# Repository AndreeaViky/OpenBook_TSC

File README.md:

# OpenBook

## Block Diagram

## Implementation steps

1. Schematic Design

   - The schematic was created based on the provided electrical diagram.
   - Components were added using the DeskAssistant library.
   - An Electrical Rules Check (ERC) was performed to ensure there were no errors or missing connections.

2. PCB Layout

   - The schematic was transferred to the PCB editor using "Switch to PCB."
   - Components were arranged according to the layout reference.
   - The board outline was drawn to the required dimensions, including necessary cutouts.
   - Key components were positioned first for visibility, while resistors and capacitors were placed based on their proximity in the schematic.
   - Auto-routing was performed on both the top and bottom layers using a 0.15 mm trace width.
   - Power traces were manually adjusted to have a minimum width of 0.30 mm for proper current handling.
   - Ground planes were created using the GND signal, followed by via stitching to improve ground continuity.
   - Most stitching vias were placed around the antenna area for enhanced grounding and RF performance.

3. 3D Components

   - 3D models were assigned in the schematic using the [Component Search Engine] (https://componentsearchengine.com).
   - Models were accurately aligned based on their footprints for realistic placement in 3D view.

4. Case Update

   - After placing the PCB inside the enclosure, the case design was modified to accommodate connectors.
   - Adjustments were made to ensure all ports were accessible and properly aligned.

5. Custom 3D Models
   - 3D models for the enclosure and display were created based on technical drawings and datasheets.
   - These models were then placed into the final assembly to verify fit and alignment.

## Bill of Materials (BOM)

| Component                | Link                                                                                                                       | Datasheet                                                                                                                                                                                                                                    |
| ------------------------ | -------------------------------------------------------------------------------------------------------------------------- | -------------------------------------------------------------------------------------------------------------------------------------------------------------------------------------------------------------------------------------------- |
| BME680                   | [Model](https://www.snapeda.com/parts/BME680/Bosch/view-part/?welcome=home)                                                | [Datasheet](//efaidnbmnnnibpcajpcglclefindmkaj/https://www.bosch-sensortec.com/media/boschsensortec/downloads/datasheets/bst-bme680-ds001.pdf)                                                                                               |
| BUTTON                   | [Model](https://industry.panasonic.com/global/en/products/control/switch/light-touch/number/evqpuj02k)                     | [Datasheet](https://www.lcsc.com/datasheet/lcsc_datasheet_2201121800_PANASONIC-EVQPUJ02K_C2936858.pdf)                                                                                                                                       |
| CAPACITOR                | [Model](<https://componentsearchengine.com/part-view/R0402%201%25%20100%20K%20(RC0402FR-07100KL)/YAGEO>)                   | [Datasheet](//efaidnbmnnnibpcajpcglclefindmkaj/https://www.resistor.com/assets/pdf/0402tstd.pdf)                                                                                                                                             |
| R0402                    | [Model](<https://componentsearchengine.com/part-view/R0402%201%25%20100%20K%20(RC0402FR-07100KL)/YAGEO>)                   | [Datasheet](//efaidnbmnnnibpcajpcglclefindmkaj/https://www.resistor.com/assets/pdf/0402tstd.pdf)                                                                                                                                             |
| CPH3225A                 | [Model](https://www.snapeda.com/parts/CPH3225A/Seiko+Instruments/view-part/?ref=eda)                                       | [Datasheet](https://octopart.com/datasheet/cph3225a-seiko-25340571)                                                                                                                                                                          |
| EVQPUJ02K                | [Model](https://industry.panasonic.com/global/en/products/control/switch/light-touch/number/evqpuj02k)                     | [Datasheet](https://www.lcsc.com/datasheet/lcsc_datasheet_2201121800_PANASONIC-EVQPUJ02K_C2936858.pdf)                                                                                                                                       |
| KP-1608SURCK             | [Model](https://www.snapeda.com/parts/KP-1608SURCK/Kingbright/view-part/?ref=search&t=LED%200603)                          | [Datasheet](//efaidnbmnnnibpcajpcglclefindmkaj/https://media.elv.com/file/107153_led_surck1608_data.pdf)                                                                                                                                     |
| USBLC6-2SC6Y             | [Model](https://www.snapeda.com/parts/USBLC6-2SC6Y/STMicroelectronics/view-part/?ref=eda)                                  | [Datasheet](https://www.digikey.com/en/htmldatasheets/production/1375342/0/0/1/usblc6-2sc6y)                                                                                                                                                 |
| SD0805S020S1R0           | [Model](https://ro.mouser.com/ProductDetail/KYOCERA-AVX/SD0805S020S1R0?qs=jCA%252BPfw4LHbpkAoSnwrdjw%3D%3D)                | [Datasheet](https://www.alldatasheet.com/view.jsp?Searchword=SD0805S&sField=2)                                                                                                                                                               |
| PGB1010603MR             | [Model](https://www.snapeda.com/parts/PGB1010603MR/Littelfuse/view-part/?ref=eda)                                          | [Datasheet](https://www.alldatasheet.com/view.jsp?Searchword=Pgb1010603mr&gad_source=1&gbraid=0AAAAADcdDU8aYfZtfJfdZ9I5j6RwZ_cbA&gclid=Cj0KCQjwqcO_BhDaARIsACz62vOPBOBe0eOh5gDUFkkKl4JBcbmoFZYtJ8BOnbaWqr_BuUCcVWvbutAaAmGkEALw_wcB)         |
| BD5229G-TR               | [Model](https://componentsearchengine.com/part-view/BD5229G-TR/ROHM%20Semiconductor)                                       | [Datasheet](https://www.lcsc.com/datasheet/lcsc_datasheet_2201131330_ROHM-Semicon-BD5229G-TR_C962636.pdf)                                                                                                                                    |
| XC6220A331MR-G           | [Model](https://componentsearchengine.com/part-view/XC6220A331MR-G/Torex)                                                  | [Datasheet](https://www.alldatasheet.com/view.jsp?Searchword=Xc6220&gad_source=1&gbraid=0AAAAADcdDU8aYfZtfJfdZ9I5j6RwZ_cbA&gclid=Cj0KCQjwqcO_BhDaARIsACz62vPS06NB6tLgniZzfaVpKNu1m811BNk6AEPfg4DbP6f5S8QWA_pW_UQaAv-0EALw_wcB)               |
| USB4110-GF-A             | [Model](<https://componentsearchengine.com/part-view/USB4110-GF-A/GCT%20(GLOBAL%20CONNECTOR%20TECHNOLOGY)>)                | [Datasheet](//efaidnbmnnnibpcajpcglclefindmkaj/https://gct.co/files/drawings/usb4110.pdf)                                                                                                                                                    |
| Adafruit LEDCHIP-LED0603 | [Model](https://eu.mouser.com/ProductDetail/Adafruit/4208?qs=PzGy0jfpSMtbScLbr0L5dw%3D%3D)                                 | [Datasheet](https://www.arrow.com/en/manufacturers/adafruit-industries/datasheets)                                                                                                                                                           |
| Bobina                   | [Model](https://store.comet.srl.ro/Catalogue/Product/43497/)                                                               | [Datasheet](https://www.scribd.com/document/814581278/Datasheet-Bobina)                                                                                                                                                                      |
| PFMF                     | [Model](https://www.mouser.co.uk/ProductDetail/EPCOS-TDK/B72520T0350K062?qs=dEfas%2FXlABIszF52uu7vrg%3D%3D)                | [Datasheet](https://ro.mouser.com/c/ds/circuit-protection/thermistors/resettable-fuses-pptc/?m=Schurter&series=PFMF)                                                                                                                         |
| DMG2305UX-7              | [Model](https://componentsearchengine.com/part-view/DMG2305UX-7/Diodes%20Incorporated)                                     | [Datasheet](//efaidnbmnnnibpcajpcglclefindmkaj/https://www.mouser.com/datasheet/2/115/DMG2305UX-266242.pdf?srsltid=AfmBOop22k34YTJJra1xubiU6LPiN4M4JlcWbRoSNdxSGFak8uWgXPpK)                                                                 |
| Si1308EDL-T1-GE3         | [Model](https://componentsearchengine.com/part-view/SI1308EDL-T1-GE3/Vishay)                                               | [Datasheet](https://www.alldatasheet.com/view.jsp?Searchword=Si1308edl&gad_source=1&gbraid=0AAAAADcdDU-px713ONYSnQ2O-gcwqYcFq&gclid=Cj0KCQjwqcO_BhDaARIsACz62vN_Nz3MJOc6J_03gnVBm7aSqC8v9wyP0VD-iRKP-gFrYgdhLi99I14aAlVJEALw_wcB)            |
| MCP73831T-5ACI/OT        | [Model](https://www.mouser.co.uk/ProductDetail/Microchip-Technology/MCP73831T-5ACI-OT?qs=hH%252BOa0VZEiAcgAcEkuamXg%3D%3D) | [Datasheet](//efaidnbmnnnibpcajpcglclefindmkaj/https://ww1.microchip.com/downloads/en/DeviceDoc/MCP73831-Family-Data-Sheet-DS20001984H.pdf)                                                                                                  |
| SMD Solder               | [Model](https://grabcad.com/library/solder-jumpers-1)                                                                      | [Datasheet]()                                                                                                                                                                                                                                |
| W25Q512JVEIQ             | [Model](https://www.snapeda.com/parts/ESP32-C6-WROOM-1-N8/Espressif+Systems/view-part/?ref=eda)                            | [Datasheet](//efaidnbmnnnibpcajpcglclefindmkaj/https://www.mouser.com/datasheet/2/949/W25Q512JV_SPI_RevB_06252019_KMS-2487502.pdf?srsltid=AfmBOoquExqDVgxEELF9CzuOGxHos0CD1nQDROHD6Eebdm2foNzqozqU)                                          |
| ESP32-C6-WROOM-1-N8      | [Model](https://www.snapeda.com/parts/ESP32-C6-WROOM-1-N8/Espressif+Systems/view-part/?ref=eda)                            | [Datasheet](//efaidnbmnnnibpcajpcglclefindmkaj/https://www.mouser.com/catalog/specsheets/Espressif_ESP32_C6_WROOM_1%20_Datasheet_V0.1_PRELIMINARY_en.pdf?srsltid=AfmBOooHQKNitqODRaaPjoZInfWKTacDER1t5uRK6sKqT13TrzvVo_B7)                   |
| DS3231SN#                | [Model](https://www.snapeda.com/parts/DS3231SN%23/Analog+Devices/view-part/?ref=eda)                                       | [Datasheet](https://www.alldatasheet.com/view.jsp?Searchword=Ds3231sn%20datasheet&gad_source=1&gbraid=0AAAAADcdDU-Gy9URfMxGmqiPg7ci5L3wR&gclid=Cj0KCQjwqcO_BhDaARIsACz62vMkK3ETSnW2w7mo0Fa-wgWJGn89AxWCyIND6k5X8MmoPl6hv6VWwT8aAiS-EALw_wcB) |
| MAX17048G+T10            | [Model](https://www.snapeda.com/parts/MAX17048G+T10/Analog+Devices/view-part/?ref=eda)                                     | [Datasheet](https://www.alldatasheet.com/view.jsp?Searchword=Max17048&gad_source=1&gbraid=0AAAAADcdDU8aYfZtfJfdZ9I5j6RwZ_cbA&gclid=Cj0KCQjwqcO_BhDaARIsACz62vNa9xrVfzjCjADRwXD0RBbo4Nret3ywwteDGLJKZui8ZL8KdVlTE7caAvQxEALw_wcB)             |

## Hardware Overview

The central unit of the system is the ESP32-C6-WROOM-1-N8, a 32-bit RISC-V microcontroller running at 160 MHz. It manages all processing tasks, communication protocols, and system control. It includes integrated support for Wi-Fi 6 (2.4 GHz) and Bluetooth 5.0, enabling reliable wireless connectivity for IoT applications.

## Power Supply & Battery Management

- Battery: Rechargeable 3.7V 1800mAh Li-Po battery, chosen for its compact size and high energy density.

- Charging Module: Based on the MCP73831T, which provides efficient and safe USB charging (5V input through USB-C).

- Voltage Regulation: A low-dropout (LDO) regulator provides a consistent 3.3V output required by the system components.

- Protections: Integrated safeguards against overcharging and deep discharge ensure long battery life and safe operation.

## Display module

- The device features a 7.5-inch E-Ink display, ideal for low-power, high-contrast applications.

- With a resolution of 800x480 pixels, it delivers sharp, readable content.

- It operates over the SPI bus, offering fast updates while minimizing power usage.

## Storage Solutions

- MicroSD Module: Offers expandable storage using FAT32, communicating via SPI.

- External NOR Flash (64MB): Provides additional non-volatile storage, also interfaced through SPI.

## Connectivity & User Input

- USB-C Port: Serves as both the power input and a communication channel, supported by ESD protection and a Schottky diode for reverse current prevention.

- Tactile Buttons: Provide manual input options for user interaction.

- Interfaces in Use:

  - GPIOs: Used for button input and other control signals

  - SPI: Shared by the SD card, flash memory, and display

  - I2C: Used by environmental sensor and RTC

  - UART: Utilized for debugging and serial monitoring

  - Wi-Fi & Bluetooth: Integrated in the ESP32-C6 for remote communication

## Errors

While editing the PCB in Fusion 360, I encountered the following errors:

The errors occurred due to the size of the holes in the PCB, so I approved them.

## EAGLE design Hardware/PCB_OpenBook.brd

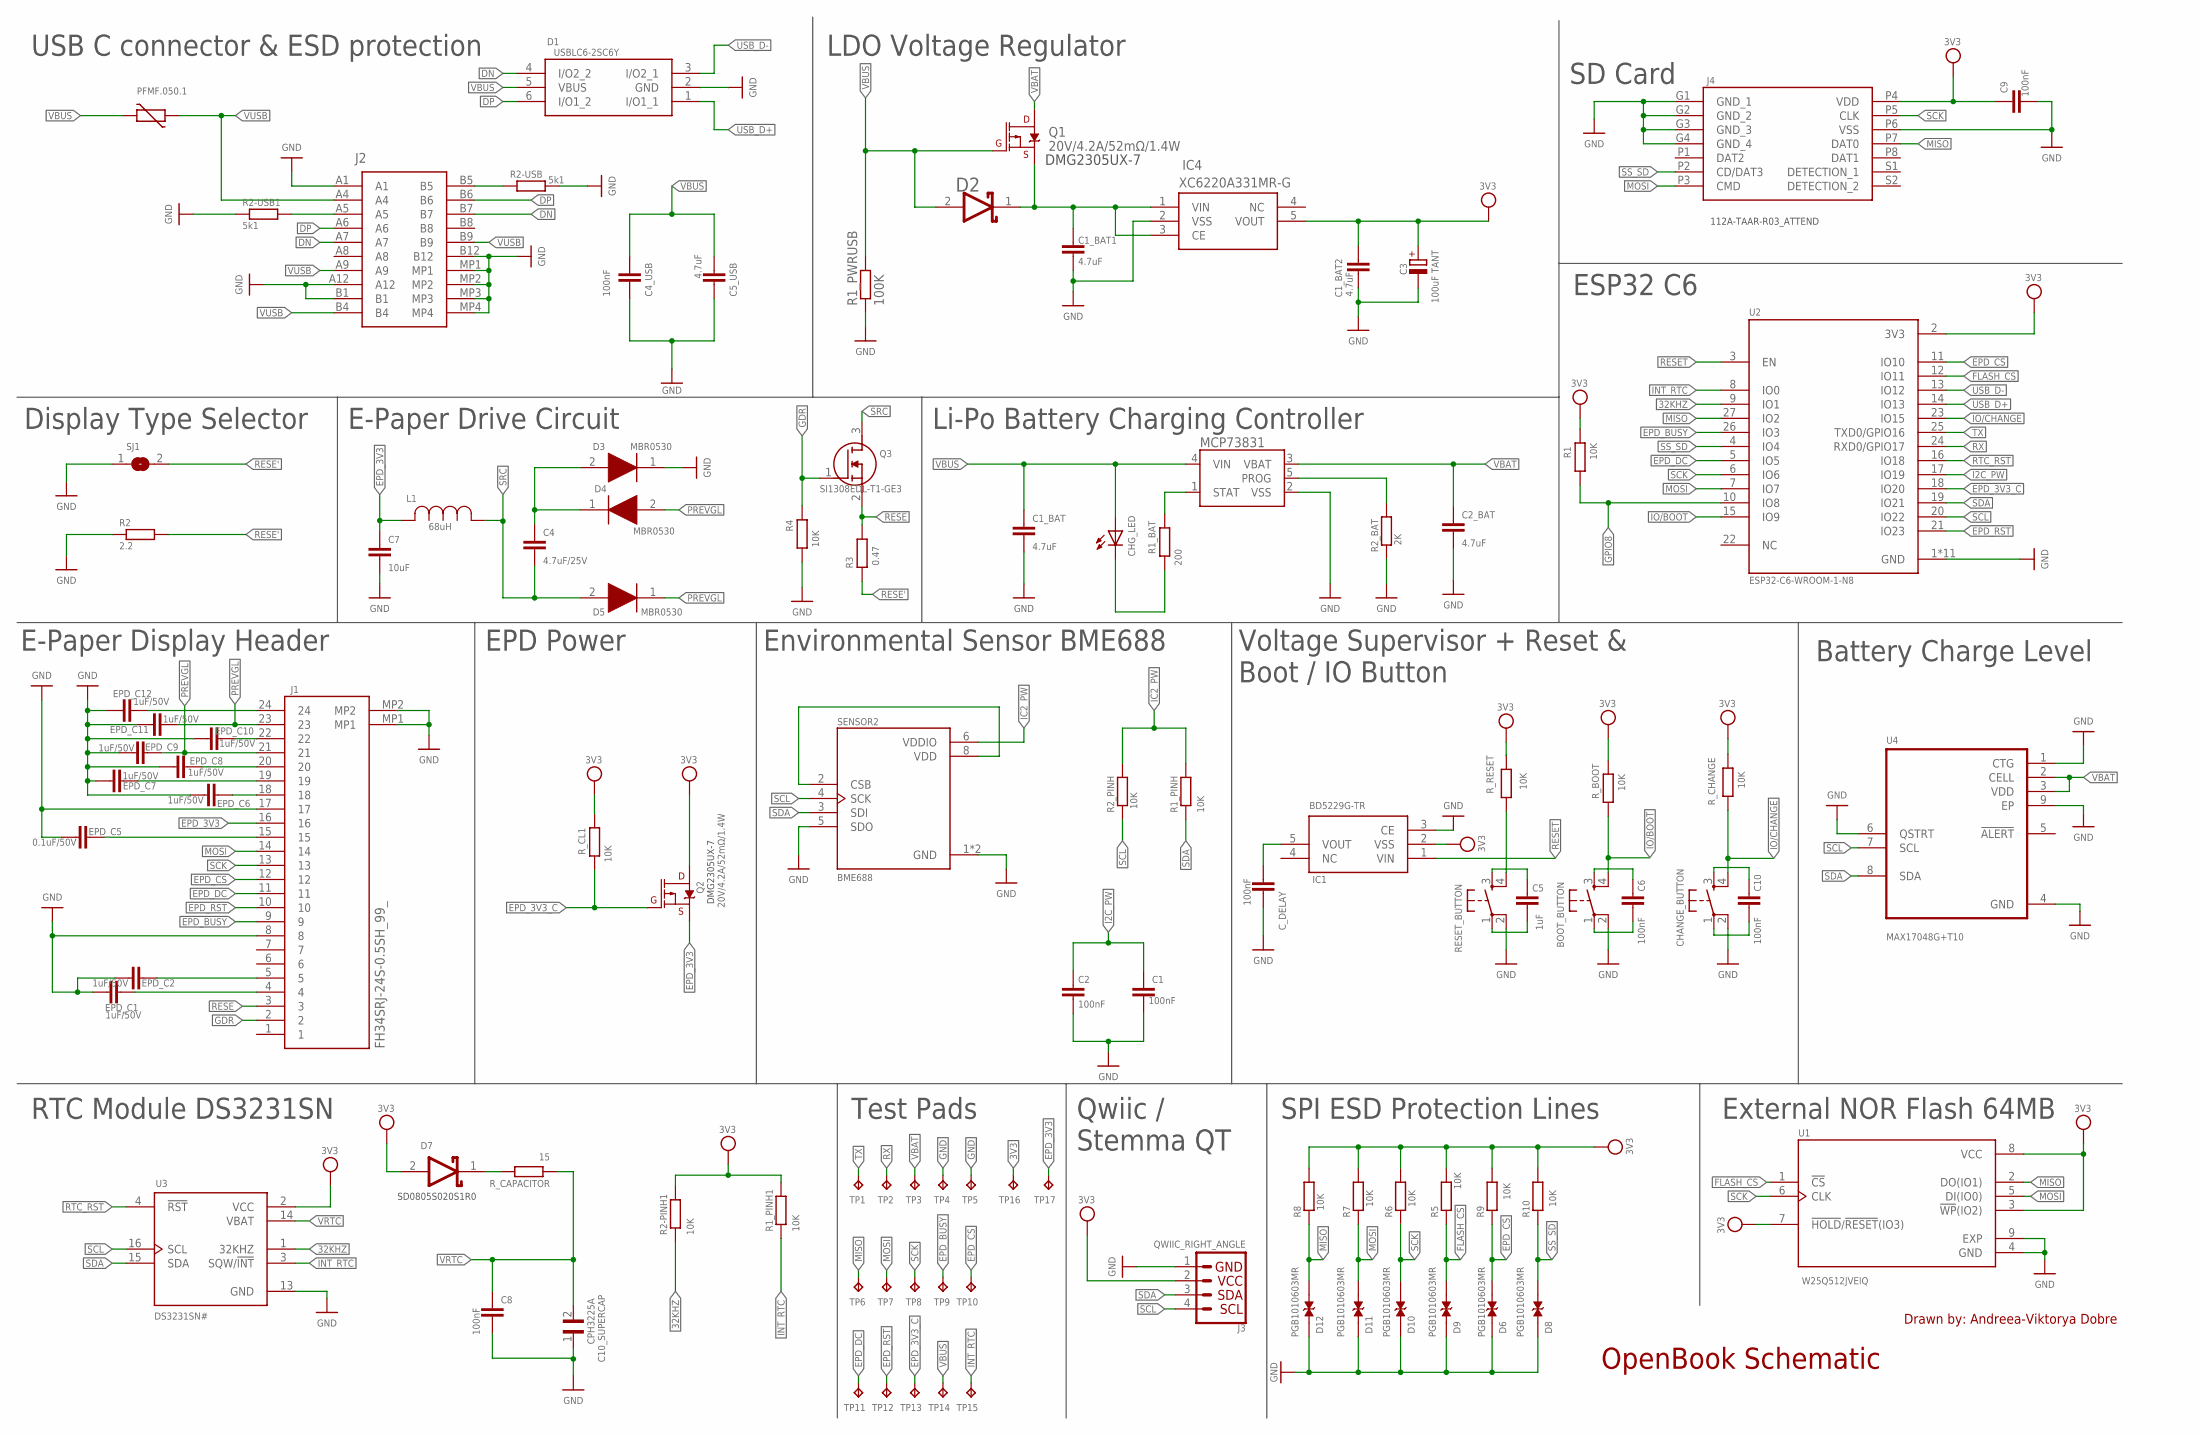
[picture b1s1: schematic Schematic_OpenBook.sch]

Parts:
BOOT_BUTTON: BUTTON_CUSYOMV1; MYBUTTON
C1, C2, C4_USB, C6, C8, C9, C10: 100nF; ESP32_WROVER_EAGLE-LTSPICE_C0402
C1_BAT, C1_BAT1, C1_BAT2, C2_BAT, C5_USB: 4.7uF; ESP32_WROVER_EAGLE-LTSPICE_C0402
C3: 100uF TANT; RCL_CT3528
C4: 4.7uF/25V; ESP32_WROVER_EAGLE-LTSPICE_C0402
C5: 1uF; ESP32_WROVER_EAGLE-LTSPICE_C0402
C7: 10uF; ESP32_WROVER_EAGLE-LTSPICE_C0402
C10_SUPERCAP: CPH3225A; CAPCP3225X100N
CHANGE_BUTTON: BUTTON_CUSYOMV1; MYBUTTON
CHG_LED: ADAFRUIT_LEDCHIP-LED0603; ADAFRUIT_CHIP-LED0603
C_DELAY: 100nF; ESP32_WROVER_EAGLE-LTSPICE_C0402
D1: USBLC6-2SC6Y; SOT95P280X145-6N
D2, D7: ESP32_WROVER_AVX---SD0805S020S1R0_AVX_SD0805S020S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; ESP32_WROVER_AVX---SD0805S020S1R0_AVX_SD0805S020S1R0_0
D3, D4, D5: MBR0530; SOD3716X135N
D6, D8, D9, D10, D11, D12: PGB1010603MR; DIOC1608X36N
EPD_C1, EPD_C2, EPD_C6, EPD_C7, EPD_C8, EPD_C9, EPD_C10, EPD_C11, EPD_C12: 1uF/50V; ESP32_WROVER_EAGLE-LTSPICE_C0402
EPD_C5: 0.1uF/50V; ESP32_WROVER_EAGLE-LTSPICE_C0402
IC1: XC6220A331MR-G; SOT95P280X120-5N; MANUFACTURER_PART_NUMBER BD5229G-TR
IC4: XC6220A331MR-G; SOT95P280X120-5N
J1: FH34SRJ-24S-0.5SH_99_; FH34SRJ24S05SH99
J2: SAMACSYS_PARTS_USB4110-GF-A; SAMACSYS_PARTS_USB4110GFA
J3: QWIIC_RIGHT_ANGLE; JST04_1MM_RA
J4: 112A-TAAR-R03_ATTEND; 112ATAARR03ATTEND
L1: 68uH; IND_4828-WE-TPC_WRE
MCP73831: ESP32_WROVER_SPARKFUN-IC-POWER_MCP73831; ESP32_WROVER_SPARKFUN-IC-POWER_SOT23-5
PFMF.050.1: ESP32C6_VARISTORCN1812; ESP32C6_VARISTOR_CT/CN1812
Q1, Q2: 20V/4.2A/52mΩ/1.4W; ESP32_WROVER_SPARKFUN-DISCRETESEMI_SOT23-3
Q3: SI1308EDL-T1-GE3; SOT65P210X110-3N
R1, R1_PINH, R1_PINH1, R2-PINH1, R2_PINH, R4, R5, R6, R7, R8, R9, R10: 10K; ESP32_WROVER_EAGLE-LTSPICE_R0402
R1_BAT: 200; ESP32_WROVER_EAGLE-LTSPICE_R0402
R1_PWRUSB: 100K; ESP32_WROVER_EAGLE-LTSPICE_R0402
R2: 2.2; ESP32_WROVER_EAGLE-LTSPICE_R0402
R2-USB, R2-USB1: 5k1; ESP32_WROVER_EAGLE-LTSPICE_R0402
R2_BAT: 2K; ESP32_WROVER_EAGLE-LTSPICE_R0402
R3: 0.47; ESP32_WROVER_EAGLE-LTSPICE_R0402
RESET_BUTTON: BUTTON_CUSYOMV1; MYBUTTON
R_BOOT: 10K; ESP32_WROVER_EAGLE-LTSPICE_R0402
R_CAPACITOR: 15; ESP32_WROVER_EAGLE-LTSPICE_R0402
R_CHANGE: 10K; ESP32_WROVER_EAGLE-LTSPICE_R0402
R_CL1: 10K; ESP32_WROVER_EAGLE-LTSPICE_R0402
R_RESET: 10K; ESP32_WROVER_EAGLE-LTSPICE_R0402
SENSOR2: BME688; ESP32_WROVER_BME680_PSON80P300X300X100-8N
SJ1: SJ
TP1, TP2, TP3, TP4, TP5, TP6, TP7, TP8, TP9, TP10, TP11, TP12, TP13, TP14, TP15, TP16, TP17: TPTP20R; TP20R
U1: W25Q512JVEIQ; SON127P600X800X80-9N
U2: ESP32-C6-WROOM-1-N8; XCVR_ESP32-C6-WROOM-1-N8
U3: DS3231SN#; SOIC127P1032X265-16N
U4: MAX17048G+T10; SON50P200X200X80-9N

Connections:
3V3: C1_BAT2.1, C3.+, C9.1, D7.2 (ANODE), IC1.2 (VSS), IC4.5 (VOUT), J3.2, J4.P4 (VDD), Q2.3 (D), R1.1, R1_PINH1.2, R2-PINH1.2, R5.2, R6.2, R7.2, R8.2, R9.2, R10.2, R_BOOT.1, R_CHANGE.1, R_CL1.1, R_RESET.1, TP16.TP, U1.3 (!WP!(IO2)), U1.7 (!HOLD!/!RESET!(IO3)), U1.8 (VCC), U2.2 (3V3), U3.2 (VCC)
32KHZ: R2-PINH1.1, U2.9 (IO1), U3.1 (32KHZ)
DN: D1.4 (I/O2_2), J2.A7, J2.B7
DP: D1.6 (I/O1_2), J2.A6, J2.B6
EPD_3V3: C7.1, J1.16, L1.2, Q2.2 (S), TP17.TP
EPD_3V3_C: Q2.1 (G), R_CL1.2, TP13.TP, U2.18 (IO20)
EPD_BUSY: J1.9, TP9.TP, U2.26 (IO3)
EPD_CS: D6.2, J1.12, R9.1, TP10.TP, U2.11 (IO10)
EPD_DC: J1.11, TP11.TP, U2.5 (IO5)
EPD_RST: J1.10, TP12.TP, U2.21 (IO23)
FLASH_CS: D9.2, R5.1, U1.1 (!CS), U2.12 (IO11)
GDR: J1.2, Q3.1 (G), R4.1
GND: BOOT_BUTTON.2, C1.2, C1_BAT.2, C1_BAT1.2, C1_BAT2.2, C2.2, C2_BAT.2, C3.-, C4_USB.2, C5_USB.2, C7.2, C8.2, C9.2, C10_SUPERCAP.1, CHANGE_BUTTON.2, C_DELAY.2, D1.2 (GND), D3.1 (K), D6.1, D8.1, D9.1, D10.1, D11.1, D12.1, EPD_C1.2, EPD_C2.2, EPD_C5.2, EPD_C6.2, EPD_C7.2, EPD_C8.2, EPD_C9.2, EPD_C10.2, EPD_C11.2, EPD_C12.2, IC1.3 (CE), IC4.2 (VSS), J1.8, J1.17, J1.MP1, J1.MP2, J2.A1, J2.A12, J2.B1, J2.B12, J2.MP1, J2.MP2, J2.MP3, J2.MP4, J3.1, J4.G1 (GND_1), J4.G2 (GND_2), J4.G3 (GND_3), J4.G4 (GND_4), J4.P6 (VSS), MCP73831.2 (VSS), R1_PWRUSB.1, R2.1, R2-USB.2, R2-USB1.1, R2_BAT.1, R4.2, RESET_BUTTON.2, SENSOR2.1 (GND), SENSOR2.5 (SDO), SENSOR2.7 (GND), SJ1.1, TP4.TP, TP5.TP, U1.4 (GND), U1.9 (EXP), U2.1 (GND), U2.28 (GND), U2.29_1 (GND), U2.29_2 (GND), U2.29_3 (GND), U2.29_4 (GND), U2.29_5 (GND), U2.29_6 (GND), U2.29_7 (GND), U2.29_8 (GND), U2.29_9 (GND), U3.13 (GND), U4.1 (CTG), U4.4 (GND), U4.6 (QSTRT), U4.9 (EP)
GPIO8: R1.2, U2.10 (IO8)
I2C_PW: C1.1, C2.1, U2.17 (IO19)
IC2_PW: R1_PINH.2, R2_PINH.2, SENSOR2.6 (VDDIO)
INT_RTC: R1_PINH1.1, TP15.TP, U2.8 (IO0), U3.3 (SQW/!INT)
IO/BOOT: BOOT_BUTTON.4, R_BOOT.2, U2.15 (IO9)
IO/CHANGE: CHANGE_BUTTON.4, R_CHANGE.2, U2.23 (IO15)
MISO: D12.2, J4.P7 (DAT0), R8.1, TP6.TP, U1.2 (DO(IO1)), U2.27 (IO2)
MOSI: D11.2, J1.14, J4.P3 (CMD), R7.1, TP7.TP, U1.5 (DI(IO0)), U2.7 (IO7)
unnamed: J2.B5, R2-USB.1
unnamed: J2.A5, R2-USB1.2
unnamed: C1_BAT1.1, D2.1 (CATHODE), IC4.1 (VIN), IC4.3 (CE), Q1.2 (S)
unnamed: C10.1, CHANGE_BUTTON.3
unnamed: C4.1, D3.2 (A), D4.1 (K)
unnamed: C10.2, CHANGE_BUTTON.1
unnamed: SENSOR2.2 (CSB), SENSOR2.8 (VDD)
unnamed: MCP73831.5 (PROG), R2_BAT.2
unnamed: EPD_C12.1, J1.24
unnamed: MCP73831.1 (STAT), R1_BAT.1
unnamed: CHG_LED.C, R1_BAT.2
unnamed: C_DELAY.1, IC1.5 (VOUT)
unnamed: EPD_C10.1, J1.22
unnamed: D7.1 (CATHODE), R_CAPACITOR.2
unnamed: EPD_C8.1, J1.20
unnamed: EPD_C7.1, J1.19
unnamed: EPD_C1.1, J1.4
unnamed: RESET_BUTTON.4, R_RESET.2
unnamed: EPD_C6.1, J1.18
unnamed: EPD_C2.1, J1.5
unnamed: EPD_C5.1, J1.15
unnamed: BOOT_BUTTON.1, C6.2
unnamed: C5.2, RESET_BUTTON.1
unnamed: BOOT_BUTTON.3, C6.1
unnamed: C5.1, RESET_BUTTON.3
PREVGL: D4.2 (A), D5.1 (K), EPD_C9.1, EPD_C11.1, J1.21, J1.23
RESE: J1.3, Q3.2 (S), R3.1
RESE': R2.2, R3.2, SJ1.2
RESET: IC1.1 (VIN), U2.3 (EN)
RTC_RST: U2.16 (IO18), U3.4 (!RST)
RX: TP2.TP, U2.24 (RXD0/GPIO17)
SCK: D10.2, J1.13, J4.P5 (CLK), R6.1, TP8.TP, U1.6 (CLK), U2.6 (IO6)
SCL: J3.4, R2_PINH.1, SENSOR2.4 (SCK), U2.20 (IO22), U3.16 (SCL), U4.7 (SCL)
SDA: J3.3, R1_PINH.1, SENSOR2.3 (SDI), U2.19 (IO21), U3.15 (SDA), U4.8 (SDA)
SRC: C4.2, D5.2 (A), L1.1, Q3.3 (D)
SS_SD: D8.2, J4.P2 (CD/DAT3), R10.1, U2.4 (IO4)
TX: TP1.TP, U2.25 (TXD0/GPIO16)
USB_D+: D1.1 (I/O1_1), U2.14 (IO13)
USB_D-: D1.3 (I/O2_1), U2.13 (IO12)
VBAT: C2_BAT.1, MCP73831.3 (VBAT), Q1.3 (D), TP3.TP, U4.2 (CELL), U4.3 (VDD)
VBUS: C1_BAT.1, C4_USB.1, C5_USB.1, CHG_LED.A, D1.5 (VBUS), D2.2 (ANODE), MCP73831.4 (VIN), PFMF.050.1.2, Q1.1 (G), R1_PWRUSB.2, TP14.TP
VRTC: C8.1, C10_SUPERCAP.2, R_CAPACITOR.1, U3.14 (VBAT)
VUSB: J2.A4, J2.A9, J2.B4, J2.B9, PFMF.050.1.1

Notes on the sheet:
USB C connector & ESD protection
LDO Voltage Regulator
DMG2305UX-7
SD Card
112A-TAAR-R03_ATTEND
Display Type Selector
Battery Charge Level
External NOR Flash 64MB
SPI ESD Protection Lines
RTC Module DS3231SN
Test Pads
Qwiic / Stemma QT
E-Paper Drive Circuit
Li-Po Battery Charging Controller
ESP32 C6
E-Paper Display Header
EPD Power
Environmental Sensor BME688
Voltage Supervisor + Reset & Boot / IO Button
SD0805S020S1R0
OpenBook Schematic
Drawn by: Andreea-Viktorya Dobre

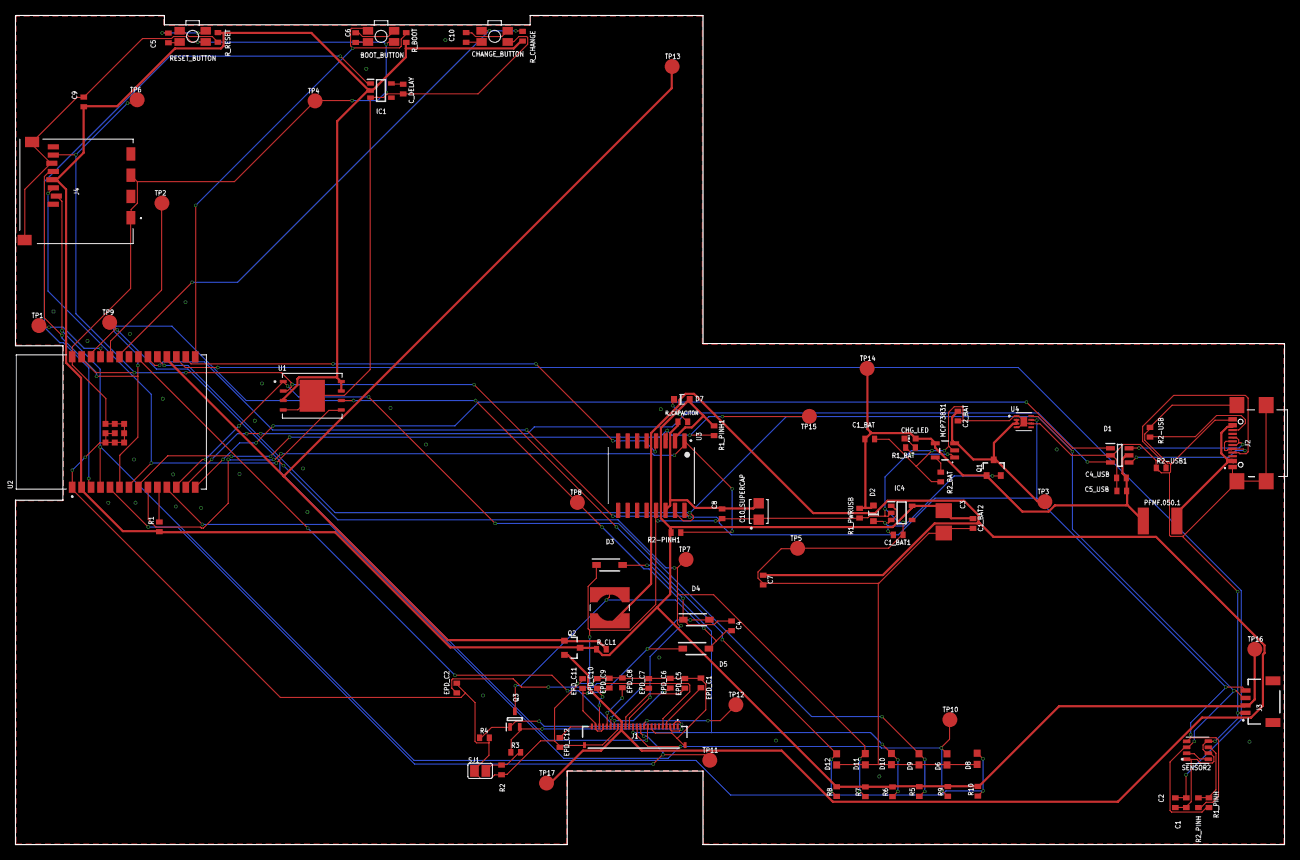
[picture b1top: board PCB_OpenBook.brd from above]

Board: 2 copper layers, 170.2 x 111.2 mm, 103 parts (0 on the bottom side), 64 nets.

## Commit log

2025-03-31 Create LICENSE
2025-04-06 Initial commit.
2025-04-06 Fix typo.
2025-04-11 Update schematic, reversing component pins
2025-04-11 Update PCB
2025-04-14 Silkscreen
2025-04-14 Update full OpenBook

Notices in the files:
parts and their libraries:
COPYRIGHT: Copyright (C) 2024 Ultra Librarian. All rights reserved.
